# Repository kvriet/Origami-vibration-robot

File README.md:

# Origami-vibration-robot
 Workshop for making origami vibration robots that walk.
 CC BY-NC Katrien van Riet

 ## Table of contents

1. [The Project](#project)
2. [Materials](#materials)
3. [Assembly](#assembly)

## The project 
This project allows children to build their own origami vibration robot. This way, children can explore folding patterns and combine these with a vibration motor to see what works for making a little robot that moves.

Once the robots have been folded, it's a nice idea to have children race their robots again each other on a flat track (maybe inclined a little).

Children can also design their own robot:

## What do I need? 
To make the robots, you need:

1. Origami paper (15x15cm)
2. Vibration motor
3. Coin cell (2032)
4. Tape
5. Googly eyes
6. Optional: decoration

## How to make the robots 

Follow the folding manual: https://github.com/kvriet/Origami-vibration-robot/blob/main/Folding%20manuals/Fold%20a%20vibration%20robot%20v1.pdf
Then tape the leads of the vibration motor to the two sides of the coin cell. Tape the vibration motor + coin cell onto the origami robot (if you want you can use double-sided tape here. Tape for fixing photographs works well here).

The robots in the pictures have custom PCBs designed by Dico Kruining and me, but tape also works. Many thanks to Dico for helping me design the PCBs and soldering them!

Your robot is now ready, but you can also decide to decorate it. Here's an example of a decorated robot:

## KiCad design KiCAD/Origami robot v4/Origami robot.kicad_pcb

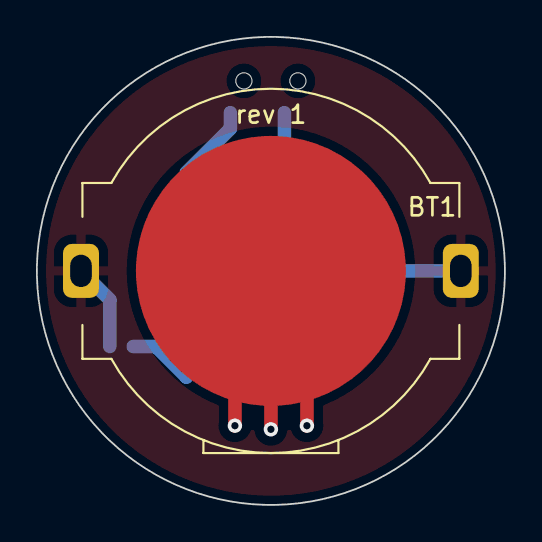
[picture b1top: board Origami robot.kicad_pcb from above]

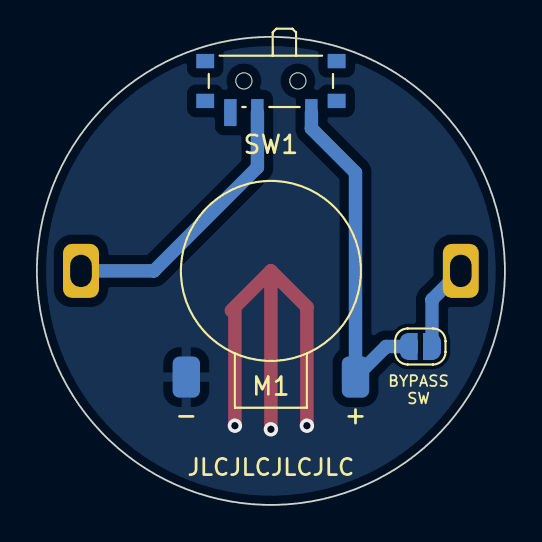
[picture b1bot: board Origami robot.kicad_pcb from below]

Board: 2 copper layers, 26.0 x 26.0 mm, 4 parts (3 on the bottom side), 3 nets.

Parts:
BT1: RS PRO CR2032 Battery Clip; BatteryHolder_RS_PRO_1x2032
JP1: SolderJumper_2_Open; SolderJumper-2_P1.3mm_Open_RoundedPad1.0x1.5mm
M1: Motor_DC; Vibration_motor
SW1: MK12C02; SW_SPDT_PCM12

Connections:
+3.3V: BT1.1 (+), JP1.2 (B), SW1.2 (B)
GND: BT1.2 (-), M1.2 (-)
unnamed: JP1.1 (A), M1.1 (+), SW1.1 (A)

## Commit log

2025-04-30 KiCAD design files for vibration motor
